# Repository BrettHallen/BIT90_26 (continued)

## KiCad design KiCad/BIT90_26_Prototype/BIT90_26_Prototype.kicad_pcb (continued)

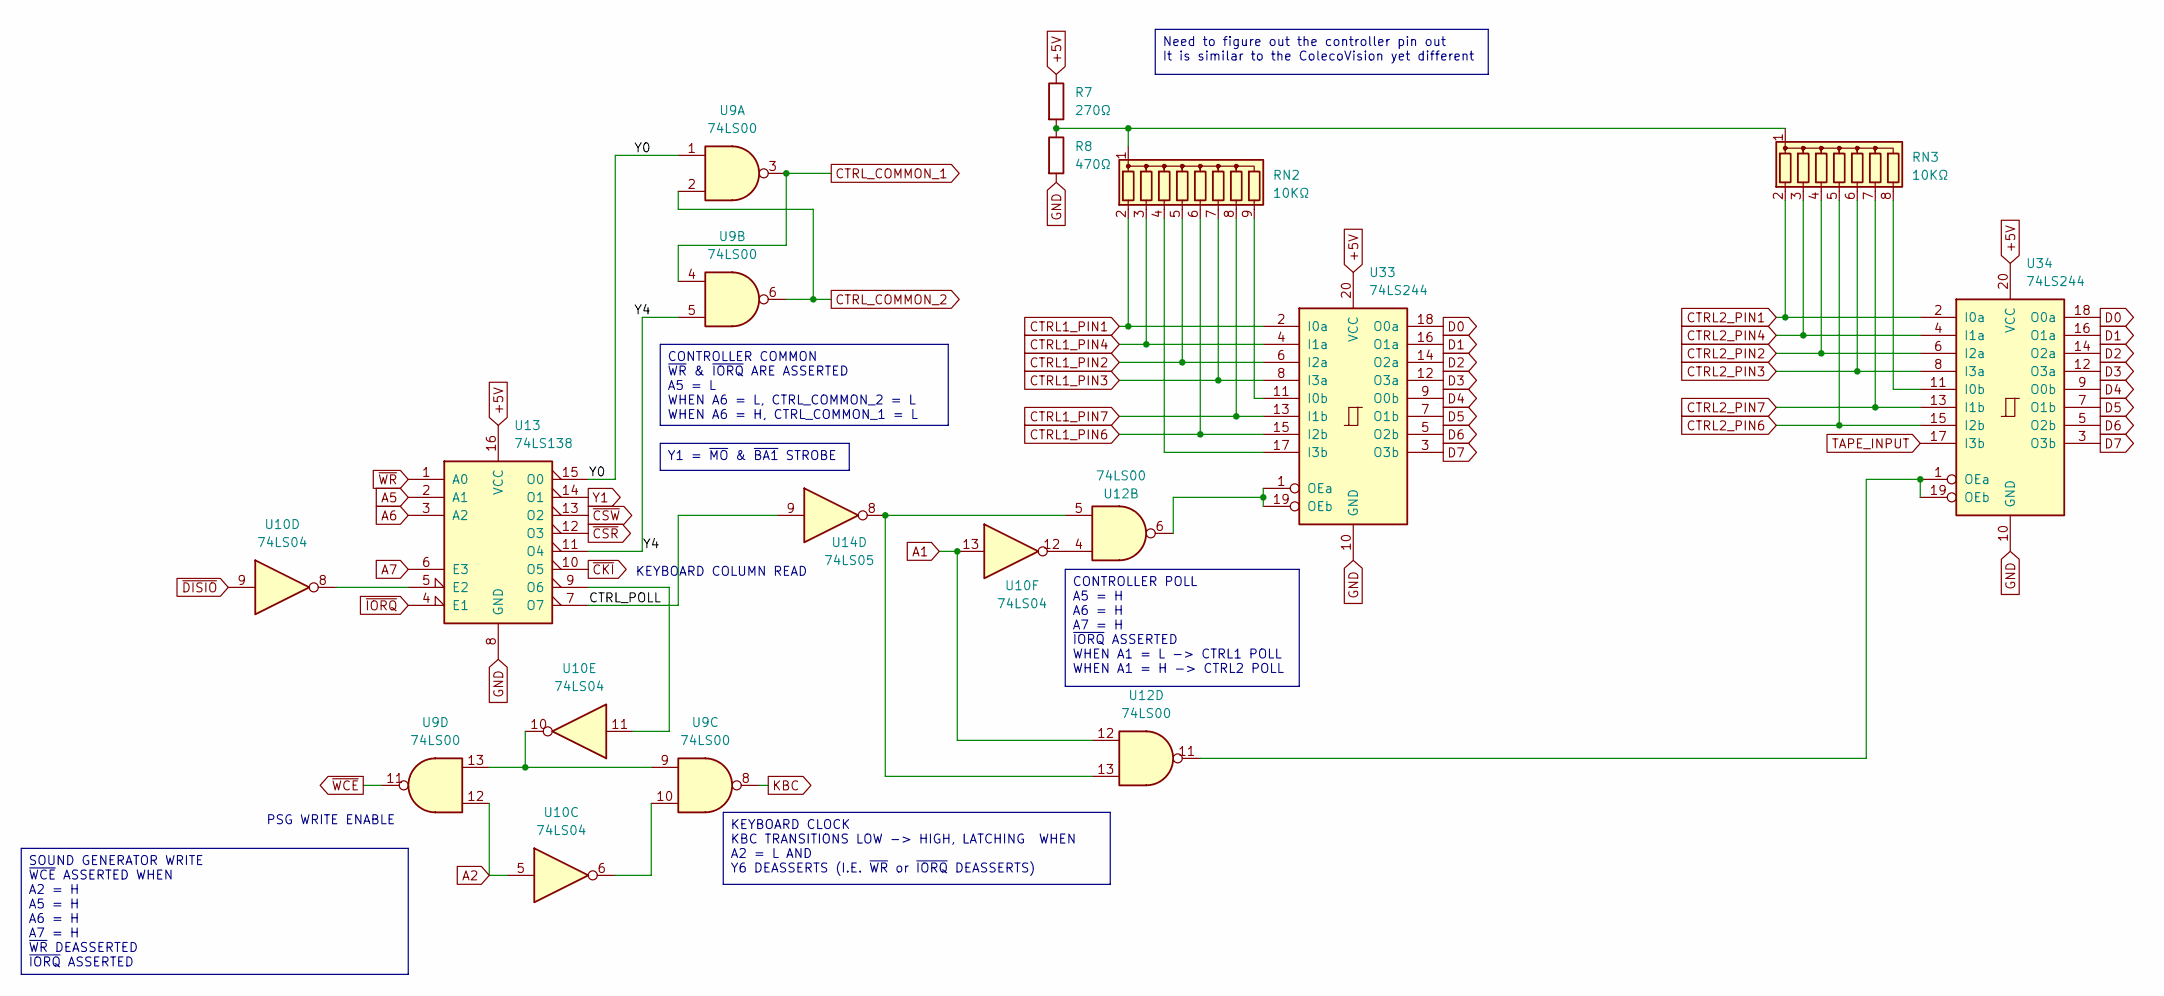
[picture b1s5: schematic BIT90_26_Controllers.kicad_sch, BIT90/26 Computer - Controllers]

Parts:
R7: 270Ω; R_Axial_DIN0207_L6.3mm_D2.5mm_P7.62mm_Horizontal
R8: 470Ω; R_Axial_DIN0207_L6.3mm_D2.5mm_P7.62mm_Horizontal
RN2: 10KΩ; R_Array_SIP9
RN3: 10KΩ; R_Array_SIP8
U9, U12: 74LS00; DIP-14_W7.62mm
U10: 74LS04; DIP-14_W7.62mm
U13: 74LS138; DIP-16_W7.62mm
U14: 74LS05; DIP-14_W7.62mm
U33, U34: 74LS244; DIP-20_W7.62mm

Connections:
+5V: R7.1, U13.16 (VCC), U33.20 (VCC), U34.20 (VCC); also elsewhere on the board
/Controllers/Y0: U9.1, U13.15 (O0)
/Controllers/Y4: U9.5, U13.11 (O4)
A1: U10.13, U12.12; also elsewhere on the board
A2: U9.12, U10.5; also elsewhere on the board
A5: U13.2 (A1); also elsewhere on the board
A6: U13.3 (A2); also elsewhere on the board
A7: U13.6 (E3); also elsewhere on the board
CTRL1_PIN1: RN2.2 (R1), U33.2 (I0a); also elsewhere on the board
CTRL1_PIN2: RN2.5 (R4), U33.6 (I2a); also elsewhere on the board
CTRL1_PIN3: RN2.7 (R6), U33.8 (I3a); also elsewhere on the board
CTRL1_PIN4: RN2.3 (R2), U33.4 (I1a); also elsewhere on the board
CTRL1_PIN6: RN2.6 (R5), U33.15 (I2b); also elsewhere on the board
CTRL1_PIN7: RN2.8 (R7), U33.13 (I1b); also elsewhere on the board
CTRL2_PIN1: RN3.2 (R1), U34.2 (I0a); also elsewhere on the board
CTRL2_PIN2: RN3.4 (R3), U34.6 (I2a); also elsewhere on the board
CTRL2_PIN3: RN3.6 (R5), U34.8 (I3a); also elsewhere on the board
CTRL2_PIN4: RN3.3 (R2), U34.4 (I1a); also elsewhere on the board
CTRL2_PIN6: RN3.5 (R4), U34.15 (I2b); also elsewhere on the board
CTRL2_PIN7: RN3.7 (R6), U34.13 (I1b); also elsewhere on the board
CTRL_COMMON_1: U9.3, U9.4; also elsewhere on the board
CTRL_COMMON_2: U9.2, U9.6; also elsewhere on the board
D0: U33.18 (O0a), U34.18 (O0a); also elsewhere on the board
D1: U33.16 (O1a), U34.16 (O1a); also elsewhere on the board
D2: U33.14 (O2a), U34.14 (O2a); also elsewhere on the board
D3: U33.12 (O3a), U34.12 (O3a); also elsewhere on the board
D4: U33.9 (O0b), U34.9 (O0b); also elsewhere on the board
D5: U33.7 (O1b), U34.7 (O1b); also elsewhere on the board
D6: U33.5 (O2b), U34.5 (O2b); also elsewhere on the board
D7: U33.3 (O3b), U34.3 (O3b); also elsewhere on the board
GND: R8.2, U13.8 (GND), U33.10 (GND), U34.10 (GND); also elsewhere on the board
KBC: U9.8; also elsewhere on the board
unnamed: RN2.4 (R3), U33.17 (I3b)
unnamed: RN2.9 (R8), U33.11 (I0b)
unnamed: R7.2, R8.1, RN2.1 (common), RN3.1 (common)
unnamed: RN3.8 (R7), U34.11 (I0b)
unnamed: U9.10, U10.6
unnamed: U9.9, U9.13, U10.10
unnamed: U10.12, U12.4
unnamed: U12.5, U12.13, U14.8
unnamed: U10.8, U13.5 (E2)
unnamed: U10.11, U13.9 (O6)
unnamed: U13.7 (O7), U14.9
unnamed: U12.6, U33.1 (OEa), U33.19 (OEb)
unnamed: U12.11, U34.1 (OEa), U34.19 (OEb)
TAPE_INPUT: U34.17 (I3b); also elsewhere on the board
Y1: U13.14 (O1); also elsewhere on the board
~CKI: U13.10 (O5); also elsewhere on the board
~CSR: U13.12 (O3); also elsewhere on the board
~CSW: U13.13 (O2); also elsewhere on the board
~DISIO: U10.9; also elsewhere on the board
~IORQ: U13.4 (E1); also elsewhere on the board
~WCE: U9.11; also elsewhere on the board
~WR: U13.1 (A0); also elsewhere on the board

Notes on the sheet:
PSG WRITE ENABLE
KEYBOARD COLUMN READ
Need to figure out the controller pin out It is similar to the ColecoVision yet different
KEYBOARD CLOCK KBC TRANSITIONS LOW -> HIGH, LATCHING WHEN A2 = L AND Y6 DEASSERTS (I.E. ~{WR} or ~{IORQ} DEASSERTS)
CONTROLLER POLL A5 = H A6 = H A7 = H ~{IORQ} ASSERTED WHEN A1 = L -> CTRL1 POLL WHEN A1 = H -> CTRL2 POLL
CONTROLLER COMMON ~{WR} & ~{IORQ} ARE ASSERTED A5 = L WHEN A6 = L, CTRL_COMMON_2 = L WHEN A6 = H, CTRL_COMMON_1 = L
Y1 = ~{MO} & ~{BA1} STROBE
SOUND GENERATOR WRITE ~{WCE} ASSERTED WHEN A2 = H A5 = H A6 = H A7 = H ~{WR} DEASSERTED ~{IORQ} ASSERTED

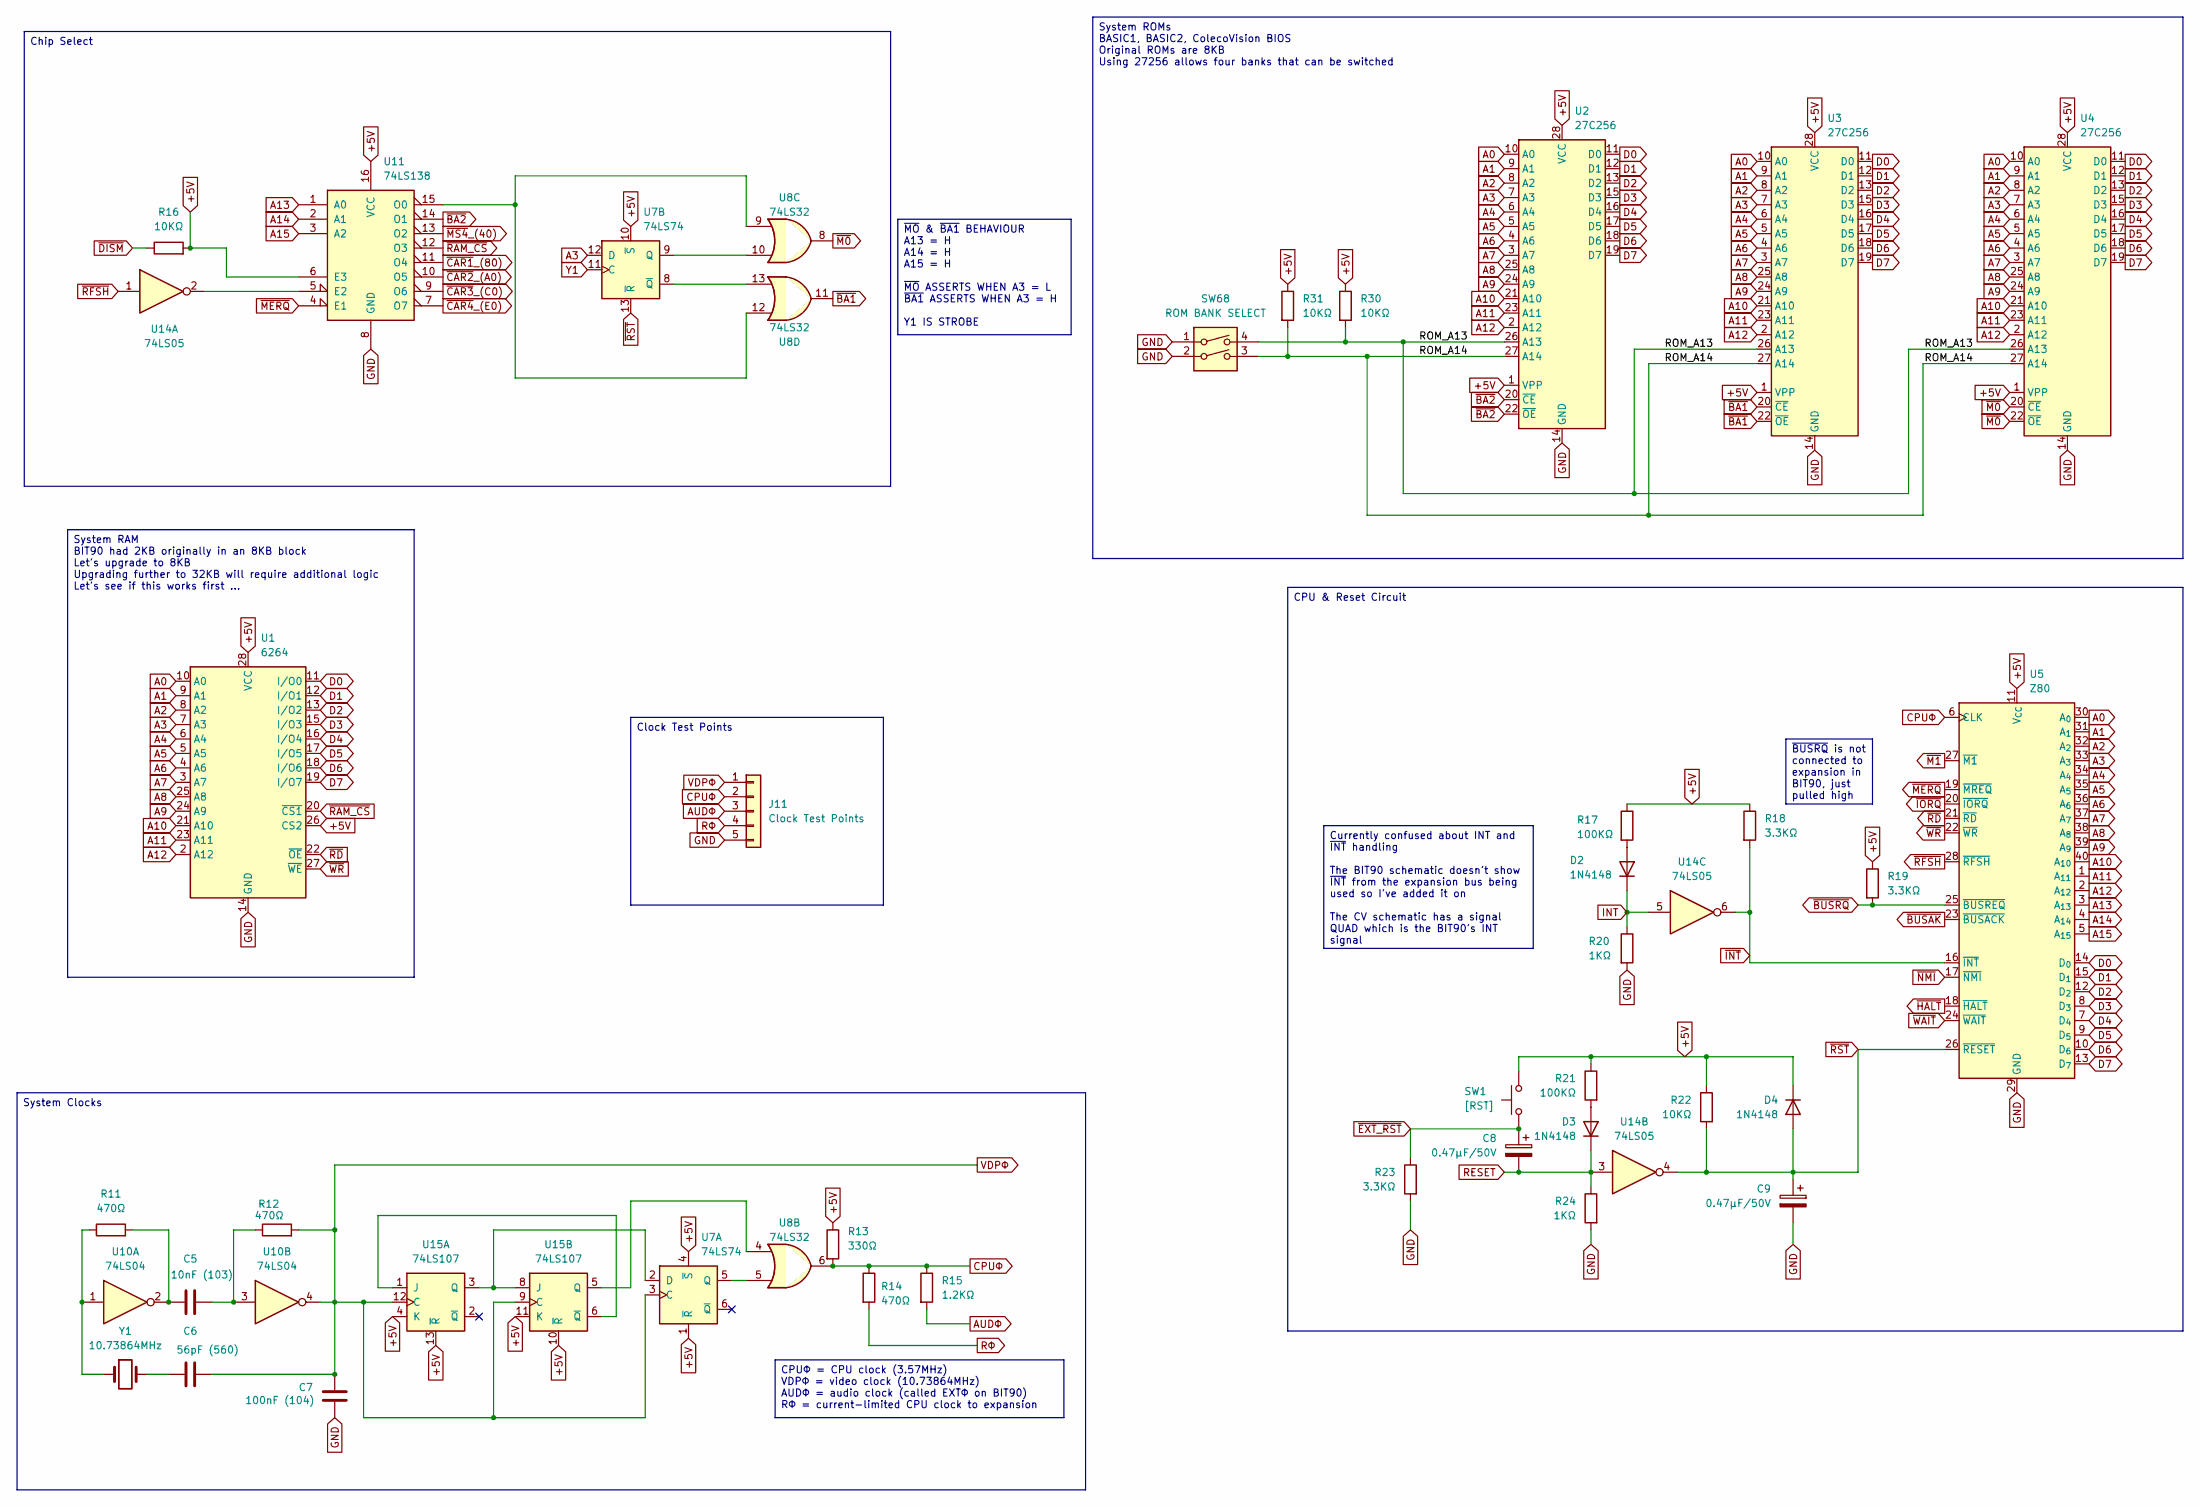
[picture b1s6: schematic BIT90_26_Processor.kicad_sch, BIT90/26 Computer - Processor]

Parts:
C5: 10nF (103); C_Disc_D3.4mm_W2.1mm_P2.50mm
C6: 56pF (560); C_Disc_D3.4mm_W2.1mm_P2.50mm
C7: 100nF (104); C_Disc_D3.4mm_W2.1mm_P2.50mm
C8, C9: 0.47µF/50V; CP_Radial_D6.3mm_P2.50mm
D2, D3, D4: 1N4148; D_DO-35_SOD27_P7.62mm_Horizontal
J11: Clock Test Points; PinHeader_1x05_P2.54mm_Vertical
R11, R12, R14: 470Ω; R_Axial_DIN0207_L6.3mm_D2.5mm_P7.62mm_Horizontal
R13: 330Ω; R_Axial_DIN0207_L6.3mm_D2.5mm_P7.62mm_Horizontal
R15: 1.2KΩ; R_Axial_DIN0207_L6.3mm_D2.5mm_P7.62mm_Horizontal
R16, R22, R30, R31: 10KΩ; R_Axial_DIN0207_L6.3mm_D2.5mm_P7.62mm_Horizontal
R17, R21: 100KΩ; R_Axial_DIN0207_L6.3mm_D2.5mm_P7.62mm_Horizontal
R18, R19, R23: 3.3KΩ; R_Axial_DIN0207_L6.3mm_D2.5mm_P7.62mm_Horizontal
R20, R24: 1KΩ; R_Axial_DIN0207_L6.3mm_D2.5mm_P7.62mm_Horizontal
SW1: [RST]; SW_Gateron_LowProfile_THT
SW68: ROM BANK SELECT; SW_DIP_SPSTx02_Slide_9.78x7.26mm_W7.62mm_P2.54mm
U1: 6264; DIP-28_W15.24mm
U2, U3, U4: 27C256; DIP-28_W15.24mm
U5: Z80; DIP-40_W15.24mm
U7: 74LS74; DIP-14_W7.62mm
U8: 74LS32; DIP-14_W7.62mm
U10: 74LS04; DIP-14_W7.62mm
U11: 74LS138; DIP-16_W7.62mm
U14: 74LS05; DIP-14_W7.62mm
U15: 74LS107; DIP-14_W7.62mm
Y1: 10.73864MHz; Crystal_HC49-U_Vertical

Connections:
+5V: D4.1 (K), R13.1, R16.2, R17.1, R18.1, R19.1, R21.1, R22.1, R30.1, R31.1, SW1.1, U1.26 (CS2), U1.28 (VCC), U2.1 (VPP), U2.28 (VCC), U3.1 (VPP), U3.28 (VCC), U4.1 (VPP), U4.28 (VCC), U5.11 (V_{CC}), U7.1 (~R), U7.4 (~S), U7.10 (~S), U11.6 (E3), U11.16 (VCC), U15.4 (K), U15.10 (~R), U15.11 (K), U15.13 (~R); also elsewhere on the board
/Processor/ROM_A13: R30.2, SW68.4, U2.26 (A13), U3.26 (A13), U4.26 (A13)
/Processor/ROM_A14: R31.2, SW68.3, U2.27 (A14), U3.27 (A14), U4.27 (A14)
A0: U1.10 (A0), U2.10 (A0), U3.10 (A0), U4.10 (A0), U5.30 (A_{0}); also elsewhere on the board
A1: U1.9 (A1), U2.9 (A1), U3.9 (A1), U4.9 (A1), U5.31 (A_{1}); also elsewhere on the board
A2: U1.8 (A2), U2.8 (A2), U3.8 (A2), U4.8 (A2), U5.32 (A_{2}); also elsewhere on the board
A3: U1.7 (A3), U2.7 (A3), U3.7 (A3), U4.7 (A3), U5.33 (A_{3}), U7.12 (D); also elsewhere on the board
A4: U1.6 (A4), U2.6 (A4), U3.6 (A4), U4.6 (A4), U5.34 (A_{4}); also elsewhere on the board
A5: U1.5 (A5), U2.5 (A5), U3.5 (A5), U4.5 (A5), U5.35 (A_{5}); also elsewhere on the board
A6: U1.4 (A6), U2.4 (A6), U3.4 (A6), U4.4 (A6), U5.36 (A_{6}); also elsewhere on the board
A7: U1.3 (A7), U2.3 (A7), U3.3 (A7), U4.3 (A7), U5.37 (A_{7}); also elsewhere on the board
A8: U1.25 (A8), U2.25 (A8), U3.25 (A8), U4.25 (A8), U5.38 (A_{8}); also elsewhere on the board
A9: U1.24 (A9), U2.24 (A9), U3.24 (A9), U4.24 (A9), U5.39 (A_{9}); also elsewhere on the board
A10: U1.21 (A10), U2.21 (A10), U3.21 (A10), U4.21 (A10), U5.40 (A_{10}); also elsewhere on the board
A11: U1.23 (A11), U2.23 (A11), U3.23 (A11), U4.23 (A11), U5.1 (A_{11}); also elsewhere on the board
A12: U1.2 (A12), U2.2 (A12), U3.2 (A12), U4.2 (A12), U5.2 (A_{12}); also elsewhere on the board
A13: U5.3 (A_{13}), U11.1 (A0); also elsewhere on the board
A14: U5.4 (A_{14}), U11.2 (A1); also elsewhere on the board
A15: U5.5 (A_{15}), U11.3 (A2); also elsewhere on the board
AUDΦ: J11.3, R15.2; also elsewhere on the board
CPUΦ: J11.2, R13.2, R14.1, R15.1, U5.6 (CLK), U8.6; also elsewhere on the board
D0: U1.11 (I/O0), U2.11 (D0), U3.11 (D0), U4.11 (D0), U5.14 (D_{0}); also elsewhere on the board
D1: U1.12 (I/O1), U2.12 (D1), U3.12 (D1), U4.12 (D1), U5.15 (D_{1}); also elsewhere on the board
D2: U1.13 (I/O2), U2.13 (D2), U3.13 (D2), U4.13 (D2), U5.12 (D_{2}); also elsewhere on the board
D3: U1.15 (I/O3), U2.15 (D3), U3.15 (D3), U4.15 (D3), U5.8 (D_{3}); also elsewhere on the board
D4: U1.16 (I/O4), U2.16 (D4), U3.16 (D4), U4.16 (D4), U5.7 (D_{4}); also elsewhere on the board
D5: U1.17 (I/O5), U2.17 (D5), U3.17 (D5), U4.17 (D5), U5.9 (D_{5}); also elsewhere on the board
D6: U1.18 (I/O6), U2.18 (D6), U3.18 (D6), U4.18 (D6), U5.10 (D_{6}); also elsewhere on the board
D7: U1.19 (I/O7), U2.19 (D7), U3.19 (D7), U4.19 (D7), U5.13 (D_{7}); also elsewhere on the board
GND: C7.1, C9.2, J11.5, R20.2, R23.2, R24.2, SW68.1, SW68.2, U1.14 (GND), U2.14 (GND), U3.14 (GND), U4.14 (GND), U5.29 (GND), U11.8 (GND); also elsewhere on the board
INT: D2.1 (K), R20.1, U14.5; also elsewhere on the board
unnamed: C5.1, R11.2, U10.2
unnamed: C5.2, R12.1, U10.3
unnamed: C6.1, Y1.2
unnamed: D2.2 (A), R17.2
unnamed: D3.2 (A), R21.2
unnamed: R11.1, U10.1, Y1.1
unnamed: U7.5 (Q), U8.5
unnamed: U7.9 (Q), U8.10
unnamed: U7.8 (~Q), U8.13
unnamed: U11.5 (E2), U14.2
unnamed: U8.9, U8.12, U11.15 (O0)
unnamed: U15.1 (J), U15.6 (~Q)
unnamed: U7.2 (D), U15.3 (Q), U15.8 (J)
unnamed: U8.4, U15.5 (Q)
RESET: C8.2, D3.1 (K), R24.1, U14.3; also elsewhere on the board
RΦ: J11.4, R14.2; also elsewhere on the board
VDPΦ: C6.2, C7.2, J11.1, R12.2, U7.3 (C), U10.4, U15.9 (C), U15.12 (C); also elsewhere on the board
Y1: U7.11 (C); also elsewhere on the board
~BA1: U3.20 (~CE), U3.22 (~OE), U8.11
~BA2: U2.20 (~CE), U2.22 (~OE), U11.14 (O1)
~BUSAK: U5.23 (~BUSACK); also elsewhere on the board
~BUSRQ: R19.2, U5.25 (~BUSREQ); also elsewhere on the board
~CAR1_(80): U11.11 (O4); also elsewhere on the board
~CAR2_(A0): U11.10 (O5); also elsewhere on the board
~CAR3_(C0): U11.9 (O6); also elsewhere on the board
~CAR4_(E0): U11.7 (O7); also elsewhere on the board
~DISM: R16.1; also elsewhere on the board
~EXT_RST: C8.1, R23.1, SW1.2; also elsewhere on the board
~HALT: U5.18 (~HALT); also elsewhere on the board
~INT: R18.2, U5.16 (~INT), U14.6; also elsewhere on the board
~IORQ: U5.20 (~IORQ); also elsewhere on the board
~M0: U4.20 (~CE), U4.22 (~OE), U8.8
~M1: U5.27 (~M1); also elsewhere on the board
~MERQ: U5.19 (~MREQ), U11.4 (E1); also elsewhere on the board
~MS4_(40): U11.13 (O2); also elsewhere on the board
~NMI: U5.17 (~NMI); also elsewhere on the board
~RAM_CS: U1.20 (~CS1), U11.12 (O3)
~RD: U1.22 (~OE), U5.21 (~RD); also elsewhere on the board
~RFSH: U5.28 (~RFSH), U14.1; also elsewhere on the board
~RST: C9.1, D4.2 (A), R22.2, U5.26 (~RESET), U7.13 (~R), U14.4; also elsewhere on the board
~WAIT: U5.24 (~WAIT); also elsewhere on the board
~WR: U1.27 (~WE), U5.22 (~WR); also elsewhere on the board

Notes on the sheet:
CPU & Reset Circuit
~{BUSRQ} is not connected to expansion in BIT90, just pulled high
System Clocks
Clock Test Points
System ROMs BASIC1, BASIC2, ColecoVision BIOS Original ROMs are 8KB Using 27256 allows four banks that can be switched
Currently confused about INT and ~{INT} handling The BIT90 schematic doesn't show ~{INT} from the expansion bus being used so I've added it on The CV schematic has a signal QUAD which is the BIT90's INT signal
Chip Select
~{MO} & ~{BA1} BEHAVIOUR A13 = H A14 = H A15 = H ~{MO} ASSERTS WHEN A3 = L ~{BA1} ASSERTS WHEN A3 = H Y1 IS STROBE
CPUΦ = CPU clock (3.57MHz) VDPΦ = video clock (10.73864MHz) AUDΦ = audio clock (called EXTΦ on BIT90) RΦ = current-limited CPU clock to expansion
System RAM BIT90 had 2KB originally in an 8KB block Let's upgrade to 8KB Upgrading further to 32KB will require additional logic Let's see if this works first ...

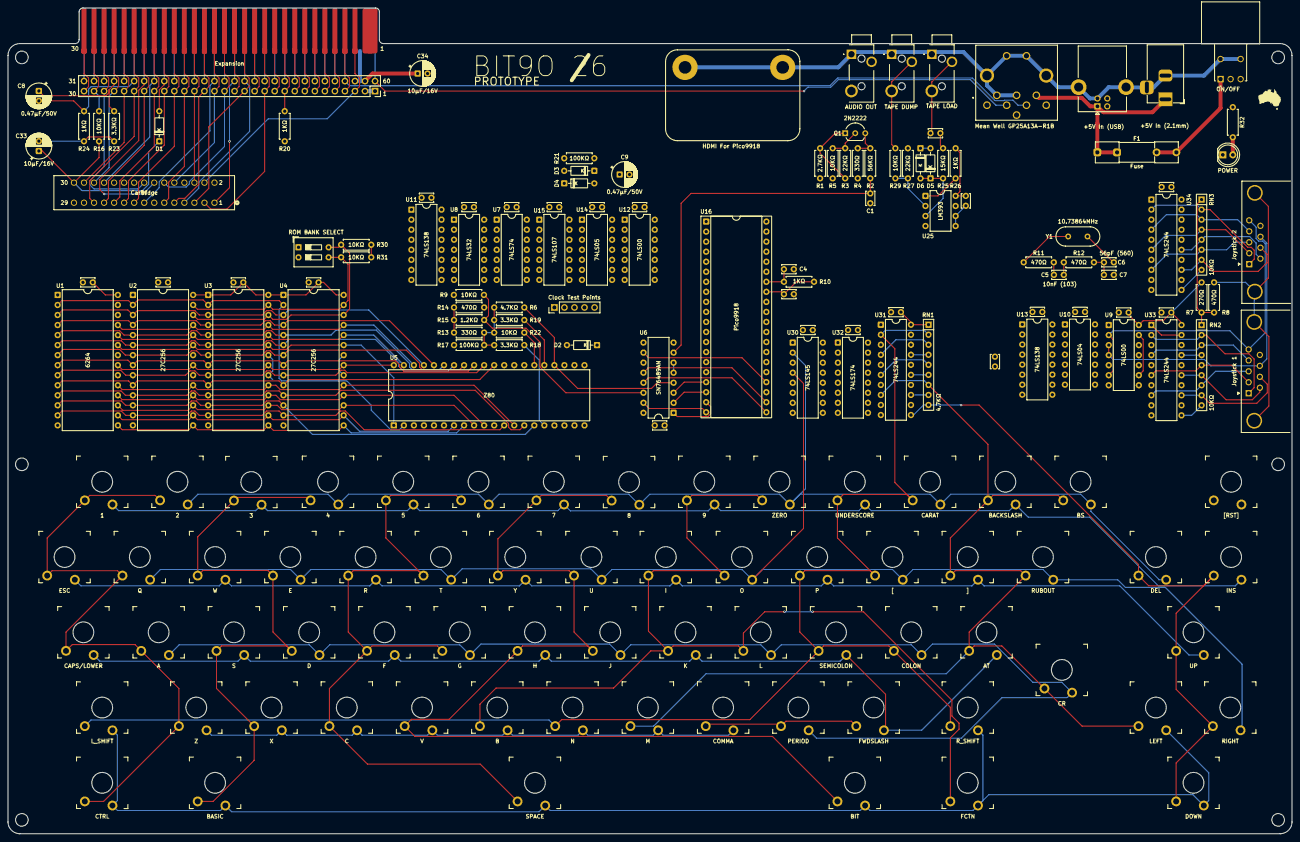
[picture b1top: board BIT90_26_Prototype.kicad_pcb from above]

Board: 2 copper layers, 325.0 x 209.0 mm, 185 parts (0 on the bottom side), 150 nets.

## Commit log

2026-06-03 Initial commit
    Very early work-in-progress on recreating original schematic
2026-06-03 Added "Processor" Sheet 6-1
2026-06-03 Completed keyboard schematic
2026-06-03 Added "Video Control" schematic
2026-06-03 Added "Joystick, Audio, Tape Out" schematic
2026-06-03 Minor schematic corrections
2026-06-03 Updated info about ROMs
    From b3rendsh info: there can be 24-pin 2364 masked ROMs, 28-pin 2764 EPROMs or a mixture.
2026-06-03 Moved redrawn schematic PDFs to own folder
2026-06-03 Completed original schematic redraw
    Well, didn't finish the Video Encoder (PAL) sheet as I'm not going to use any of it in the new design.
    Moved the audio output from that sheet to the Joystick/Audio/Tape out sheet where the sound generator is.
2026-06-04 Keyboard layout created
2026-06-05 Added useful references
    Just a backup in case original links, sites, Google Drives, disappear ... this is likely vital information that needs to be referenced in 2076!
2026-06-05 Resolving BIT90 schematic errors #1
    The original BIT90 schematic was confusing as the controller/joystick buffer enable pins were wired weirdly. But thanks to motherboard underside photo from Henk & CV schematics, resolved!
2026-06-05 Small updates/corrections
    Managed to figure out some more errors/missing info from ColecoVision schematics & Henk's BIT90 motherboard underside photo
2026-06-05 Resolved audio clock signal
    Marked as EXTΦ on BIT90 schematic, generated via resistor from CPUΦ
    Renamed it as AUDΦ so it's a bit clearer
2026-06-05 Initial redesign completed
    Most errors are expansion bus signals that aren't connected anywhere else
2026-06-05 Minor schematic update
    Henk: On my system board the R7 and C14 components are not mounted on the PCB.
2026-06-06 Minor corrections & footprints assigned
    PCB layout started
2026-06-06 Minor corrections
2026-06-06 PCB layout started
2026-06-07 Moved initial design to Prototype folder
2026-06-07 Added more signal analysis to schematic
    Would be nice to reduce the amount of glue logic
2026-06-07 Started revised design using GALs
    Removing some glue logic to try to simplify the PCB routing
    Removed 74LS74, 74LS107, 74LS32, 74LS00
